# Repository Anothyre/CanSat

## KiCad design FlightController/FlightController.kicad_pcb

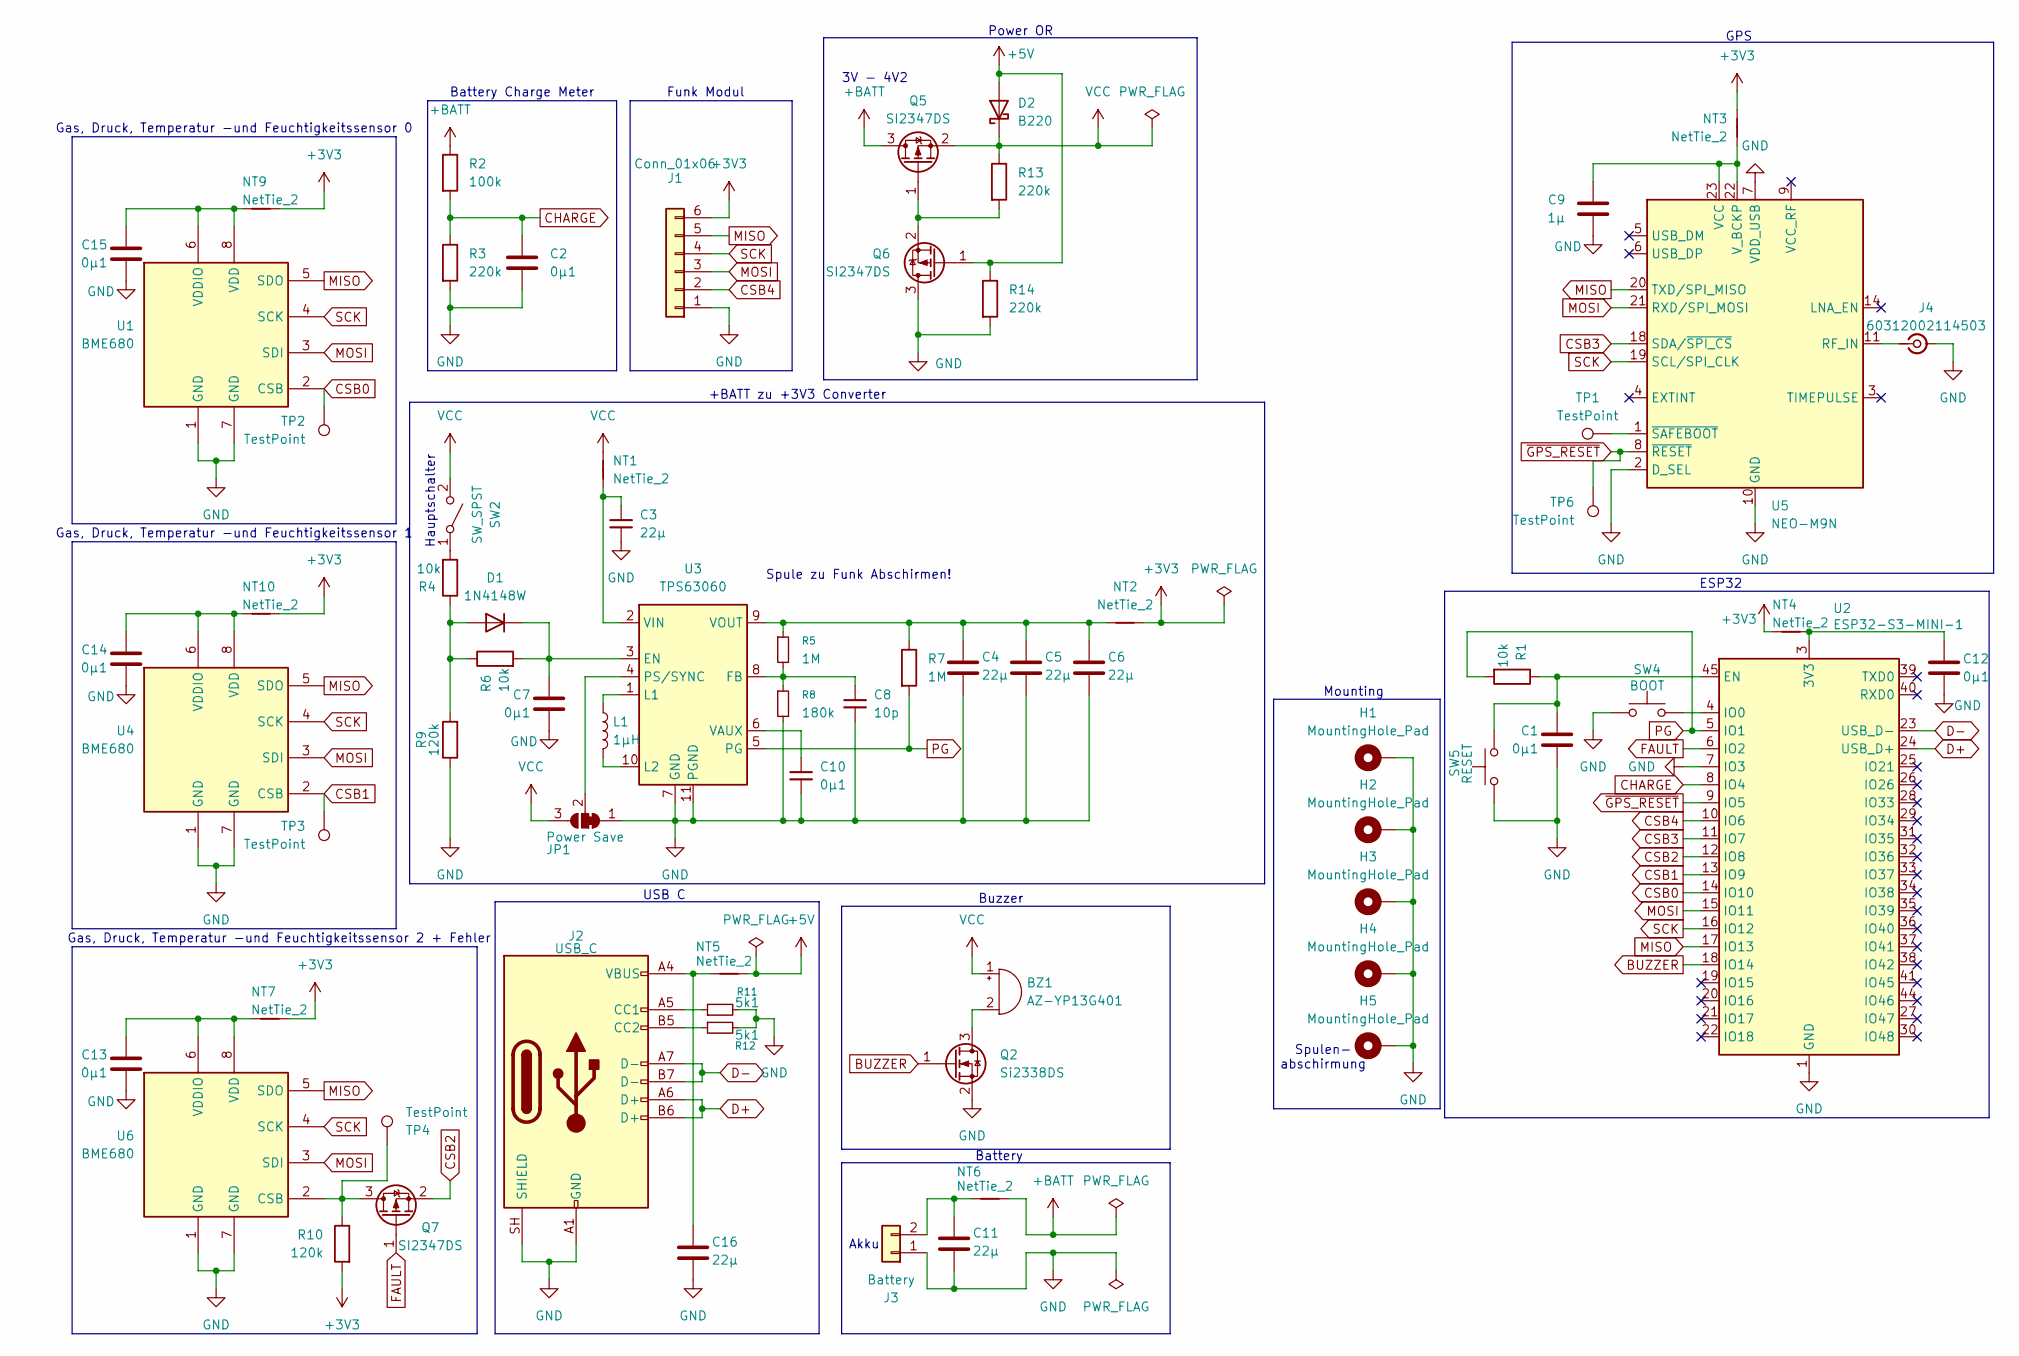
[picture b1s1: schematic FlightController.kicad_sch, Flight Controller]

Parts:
BZ1: AZ-YP13G401; MagneticBuzzer_ProSignal_ABT-410-RC
C1, C2, C7, C10, C12, C13, C14, C15: 0µ1; C_0805_2012Metric_Pad1.18x1.45mm_HandSolder
C3, C4, C5, C6, C11, C16: 22µ; C_0805_2012Metric_Pad1.18x1.45mm_HandSolder
C8: 10p; C_0805_2012Metric_Pad1.18x1.45mm_HandSolder
C9: 1µ; C_0805_2012Metric_Pad1.18x1.45mm_HandSolder
D1: 1N4148W; D_SOD-123
D2: B220; D_SMB
H1, H2, H3, H4: MountingHole_Pad; MountingHole_3.2mm_M3_DIN965_Pad_TopBottom
H5: MountingHole_Pad; MountingHole_2.2mm_M2_DIN965_Pad_TopBottom
J1: Conn_01x06; PinHeader_1x06_P2.54mm_Vertical
J2: USB_C; USB_C_Receptacle_HRO_TYPE-C-31-M-12
J3: Battery; JST-PH-2
J4: 60312002114503; SMA_Wurth_60312002114503_Vertical
JP1: Power Save; SolderJumper-3_P1.3mm_Bridged12_RoundedPad1.0x1.5mm
L1: 1µH; L_Coilcraft_XxL4020
NT1, NT2, NT3, NT4, NT5, NT6, NT7, NT9, NT10: NetTie_2; NetTie-2_SMD_Pad0.5mm
Q2: Si2338DS; SOT-23
Q5, Q6, Q7: SI2347DS; SOT-23
R1, R4, R6: 10k; R_0805_2012Metric_Pad1.20x1.40mm_HandSolder
R2: 100k; R_0805_2012Metric_Pad1.20x1.40mm_HandSolder
R3, R13, R14: 220k; R_0805_2012Metric_Pad1.20x1.40mm_HandSolder
R5, R7: 1M; R_0805_2012Metric_Pad1.20x1.40mm_HandSolder
R8: 180k; R_0805_2012Metric_Pad1.20x1.40mm_HandSolder
R9, R10: 120k; R_0805_2012Metric_Pad1.20x1.40mm_HandSolder
R11, R12: 5k1; R_0805_2012Metric_Pad1.20x1.40mm_HandSolder
SW2: SW_SPST; PinHeader_1x02_P2.54mm_Vertical
SW4: BOOT; SW_Push_5.1mm_H1.5mm
SW5: RESET; SW_Push_5.1mm_H1.5mm
TP1, TP2, TP3, TP4, TP6: TestPoint; TestPoint_Pad_D1.0mm
U1, U4, U6: BME680; Bosch_LGA-8_3x3mm_P0.8mm_ClockwisePinNumbering
U2: ESP32-S3-MINI-1
U3: TPS63060; Texas_DSC0010J_ThermalVias
U5: NEO-M9N; ublox_NEO

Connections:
+5V: D2.2 (A), NT5.2, Q6.1 (G), R14.1
+BATT: NT6.2, Q5.3 (D), R2.1
BUZZER: Q2.1 (G), U2.18 (IO14)
CHARGE: C2.1, R2.2, R3.1, U2.8 (IO4)
CSB0: TP2.1 (1_1), U1.2 (CSB), U2.14 (IO10)
CSB1: TP3.1 (1_1), U2.13 (IO9), U4.2 (CSB)
CSB2: Q7.2 (S), U2.12 (IO8)
CSB3: U2.11 (IO7), U5.18 (SDA/~SPI_CS)
CSB4: J1.2, U2.10 (IO6)
D+: J2.A6 (D+), J2.B6 (D+), U2.24 (USB_D+)
D-: J2.A7 (D-), J2.B7 (D-), U2.23 (USB_D-)
FAULT: Q7.1 (G), U2.6 (IO2)
GND: C1.2, C2.2, C3.2, C4.2, C5.2, C6.2, C7.2, C8.2, C9.2, C10.2, C11.2, C12.2, C13.2, C14.2, C15.2, C16.2, H1.1 (1_1), H2.1 (1_1), H3.1 (1_1), H4.1 (1_1), H5.1 (1_1), J1.1, J2.A1 (GND), J2.A12 (GND), J2.B1 (GND), J2.B12 (GND), J2.SH (SHIELD), J3.1, J4.2 (Ext), JP1.1 (A), Q2.2 (S), Q6.3 (D), R3.2, R8.2, R9.1, R11.2, R12.2, R14.2, SW4.1, SW5.1, U1.1 (GND), U1.7 (GND), U2.1 (GND), U2.2 (GND), U2.7 (IO3), U2.42 (GND), U2.43 (GND), U2.46 (GND), U2.47 (GND), U2.48 (GND), U2.49 (GND), U2.50 (GND), U2.51 (GND), U2.52 (GND), U2.53 (GND), U2.54 (GND), U2.55 (GND), U2.56 (GND), U2.57 (GND), U2.58 (GND), U2.59 (GND), U2.60 (GND), U2.61 (GND), U2.62 (GND), U2.63 (GND), U2.64 (GND), U2.65 (GND), U3.7 (GND), U3.11 (PGND), U4.1 (GND), U4.7 (GND), U5.2 (D_SEL), U5.7 (VDD_USB), U5.10 (GND), U5.12 (GND), U5.13 (GND), U5.24 (GND), U6.1 (GND), U6.7 (GND)
MISO: J1.5, U1.5 (SDO), U2.17 (IO13), U4.5 (SDO), U5.20 (TXD/SPI_MISO), U6.5 (SDO)
MOSI: J1.3, U1.3 (SDI), U2.15 (IO11), U4.3 (SDI), U5.21 (RXD/SPI_MOSI), U6.3 (SDI)
unnamed: BZ1.2 (-), Q2.3 (D)
unnamed: C16.1, J2.A4 (VBUS), J2.A9 (VBUS), J2.B4 (VBUS), J2.B9 (VBUS), NT5.1
unnamed: D1.2 (A), R4.1, R6.1, R9.2
unnamed: C7.1, D1.1 (K), R6.2, U3.3 (EN)
unnamed: J2.A5 (CC1), R11.1
unnamed: J2.B5 (CC2), R12.1
unnamed: C11.1, J3.2, NT6.1
unnamed: J4.1 (In), U5.11 (RF_IN)
unnamed: JP1.2 (C), U3.4 (PS/SYNC)
unnamed: Q5.1 (G), Q6.2 (S), R13.2
unnamed: Q7.3 (D), R10.1, TP4.1 (1_1), U6.2 (CSB)
unnamed: R4.2, SW2.1 (A)
unnamed: C15.1, NT9.1, U1.6 (VDDIO), U1.8 (VDD)
unnamed: C12.1, NT4.2, U2.3 (3V3)
unnamed: C1.1, R1.1, SW5.2, U2.45 (EN)
unnamed: SW4.2, U2.4 (IO0)
unnamed: C8.1, R5.2, R8.1, U3.8 (FB)
unnamed: L1.1, U3.1 (L1)
unnamed: L1.2, U3.10 (L2)
unnamed: C10.1, U3.6 (VAUX)
unnamed: C3.1, NT1.1, U3.2 (VIN)
unnamed: C4.1, C5.1, C6.1, NT2.1, R5.1, R7.1, U3.9 (VOUT)
unnamed: C14.1, NT10.1, U4.6 (VDDIO), U4.8 (VDD)
unnamed: C9.1, NT3.1, U5.22 (V_BCKP), U5.23 (VCC)
unnamed: TP1.1 (1_1), U5.1 (~SAFEBOOT)
unnamed: C13.1, NT7.1, U6.6 (VDDIO), U6.8 (VDD)
SCK: J1.4, U1.4 (SCK), U2.16 (IO12), U4.4 (SCK), U5.19 (SCL/SPI_CLK), U6.4 (SCK)
VCC: BZ1.1 (+), D2.1 (K), JP1.3 (B), NT1.2, Q5.2 (S), R13.1, SW2.2 (B)
~GPS_RESET: TP6.1 (1_1), U2.9 (IO5), U5.8 (~RESET)

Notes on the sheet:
Battery Charge Meter
Power OR
USB C
Spule zu Funk Abschirmen!
+BATT zu +3V3 Converter
ESP32
3V - 4V2
Funk Modul
Gas, Druck, Temperatur -und Feuchtigkeitssensor 1
Gas, Druck, Temperatur -und Feuchtigkeitssensor 2 + Fehler
Gas, Druck, Temperatur -und Feuchtigkeitssensor 0
Akku
Mounting
Hauptschalter
GPS
Buzzer
Spulen- abschirmung
Battery

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
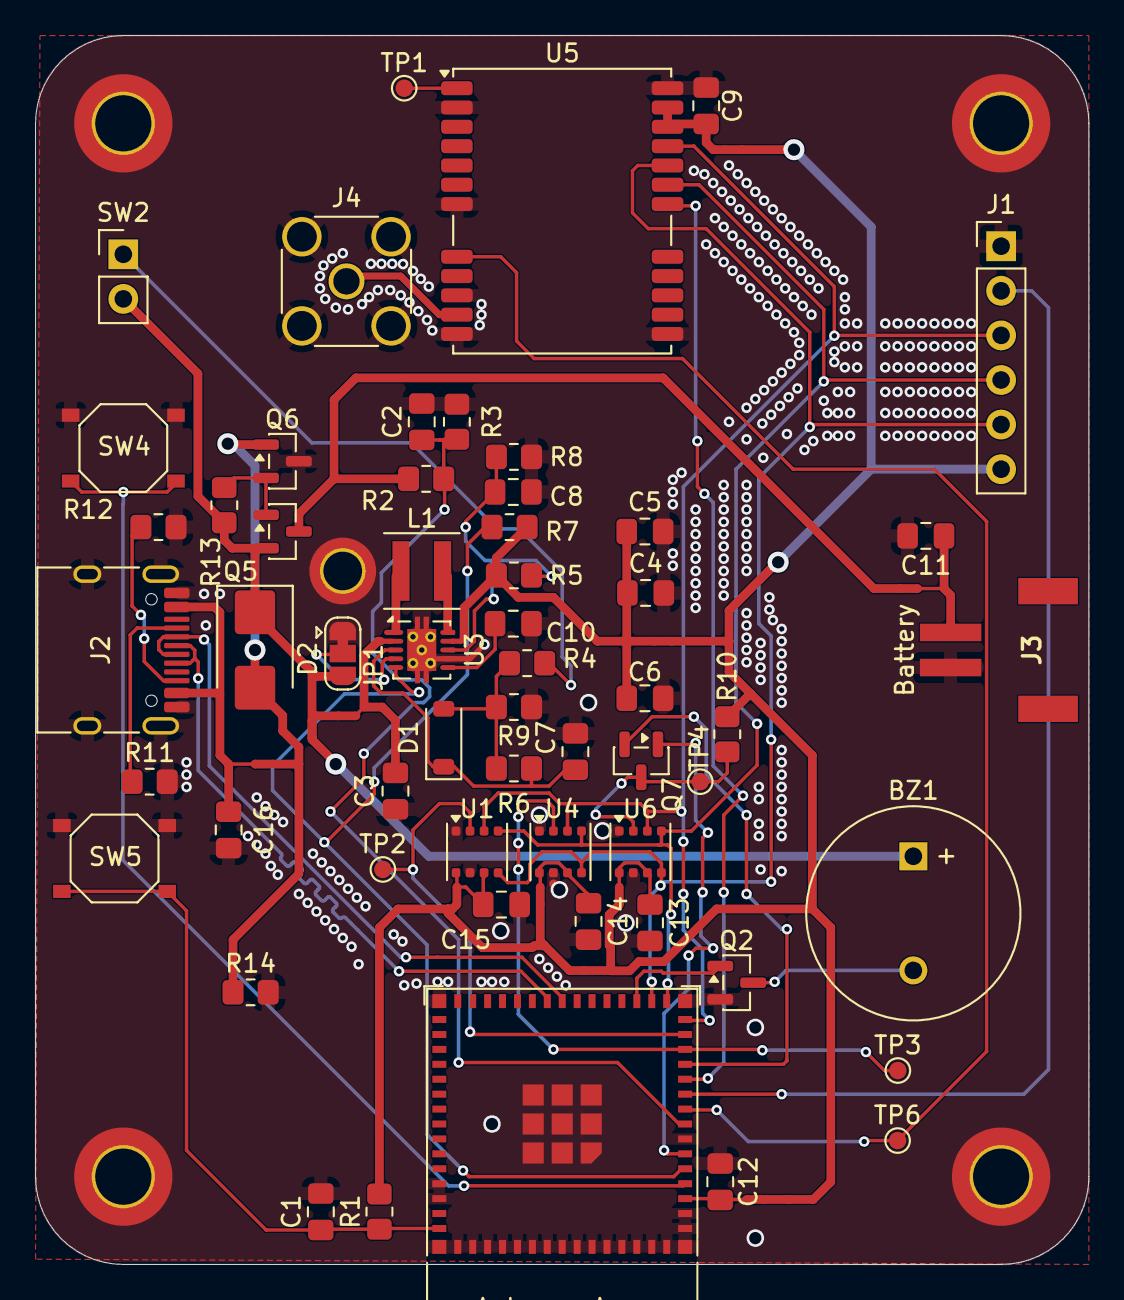
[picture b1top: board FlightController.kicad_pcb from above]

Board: 2 copper layers, 60.0 x 70.0 mm, 71 parts (0 on the bottom side), 46 nets.

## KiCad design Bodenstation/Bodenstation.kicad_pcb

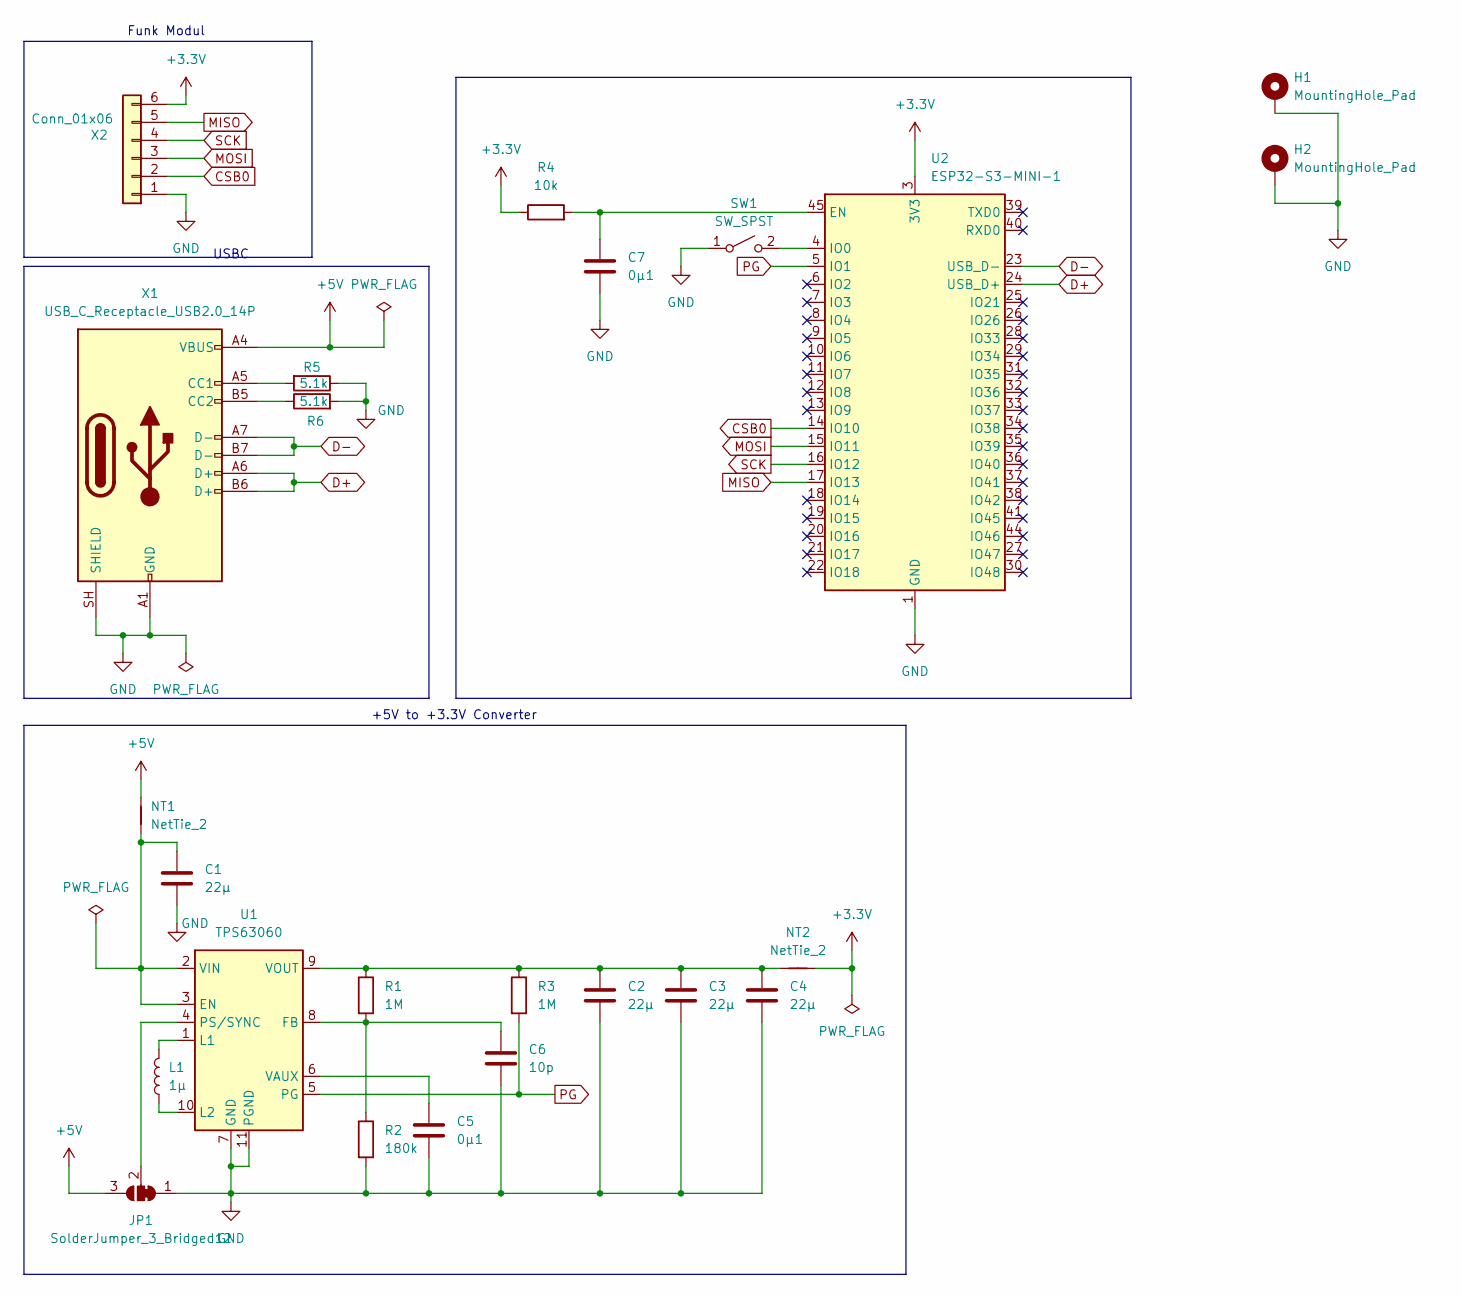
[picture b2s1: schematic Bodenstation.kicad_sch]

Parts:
C1, C2, C3, C4: 22µ; C_0805_2012Metric_Pad1.18x1.45mm_HandSolder
C5, C7: 0µ1; C_0805_2012Metric_Pad1.18x1.45mm_HandSolder
C6: 10p; C_0805_2012Metric_Pad1.18x1.45mm_HandSolder
H1, H2: MountingHole_Pad; MountingHole_3.2mm_M3
JP1: SolderJumper_3_Bridged12; WSON-8-1EP_6x5mm_P1.27mm_EP3.4x4mm
L1: 1µ; L_Coilcraft_XxL4020
NT1, NT2: NetTie_2; NetTie-2_SMD_Pad0.5mm
R1, R3: 1M; R_0805_2012Metric_Pad1.20x1.40mm_HandSolder
R2: 180k; R_0805_2012Metric_Pad1.20x1.40mm_HandSolder
R4: 10k; R_0805_2012Metric_Pad1.20x1.40mm_HandSolder
R5, R6: 5.1k; R_0805_2012Metric_Pad1.20x1.40mm_HandSolder
SW1: SW_SPST; SW_Push_5.1mm_H1.5mm
U1: TPS63060; Texas_S-PWSON-N10_ThermalVias
U2: ESP32-S3-MINI-1; ESP32-S2-MINI-1
X1: USB_C_Receptacle_USB2.0_14P; USB_C_Receptacle_HRO_TYPE-C-31-M-12
X2: Conn_01x06; PinHeader_1x06_P2.54mm_Vertical

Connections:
+3.3V: NT2.1, R4.1, U2.3 (3V3), X2.6
+5V: JP1.3 (B), NT1.2, X1.A4 (VBUS), X1.A9 (VBUS), X1.B4 (VBUS), X1.B9 (VBUS)
CSB0: U2.14 (IO10), X2.2
D+: U2.24 (USB_D+), X1.A6 (D+), X1.B6 (D+)
D-: U2.23 (USB_D-), X1.A7 (D-), X1.B7 (D-)
GND: C1.2, C2.2, C3.2, C4.2, C5.2, C6.2, C7.2, H1.1, H2.1, JP1.1 (A), R2.2, R5.1, R6.2, SW1.1 (A), U1.7 (GND), U1.11 (PGND), U2.1 (GND), U2.2 (GND), U2.42 (GND), U2.43 (GND), U2.46 (GND), U2.47 (GND), U2.48 (GND), U2.49 (GND), U2.50 (GND), U2.51 (GND), U2.52 (GND), U2.53 (GND), U2.54 (GND), U2.55 (GND), U2.56 (GND), U2.57 (GND), U2.58 (GND), U2.59 (GND), U2.60 (GND), U2.61 (GND), U2.62 (GND), U2.63 (GND), U2.64 (GND), U2.65 (GND), X1.A1 (GND), X1.A12 (GND), X1.B1 (GND), X1.B12 (GND), X1.SH (SHIELD), X2.1
MISO: U2.17 (IO13), X2.5
MOSI: U2.15 (IO11), X2.3
unnamed: JP1.2 (C), U1.4 (PS/SYNC)
unnamed: SW1.2 (B), U2.4 (IO0)
unnamed: C1.1, NT1.1, U1.2 (VIN), U1.3 (EN)
unnamed: C6.1, R1.2, R2.1, U1.8 (FB)
unnamed: L1.2, U1.1 (L1)
unnamed: L1.1, U1.10 (L2)
unnamed: C5.1, U1.6 (VAUX)
unnamed: C2.1, C3.1, C4.1, NT2.2, R1.1, R3.1, U1.9 (VOUT)
unnamed: C7.1, R4.2, U2.45 (EN)
unnamed: R5.2, X1.A5 (CC1)
unnamed: R6.1, X1.B5 (CC2)
PG: R3.2, U1.5 (PG), U2.5 (IO1)
SCK: U2.16 (IO12), X2.4

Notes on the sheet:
+5V to +3.3V Converter
USBC
Funk Modul

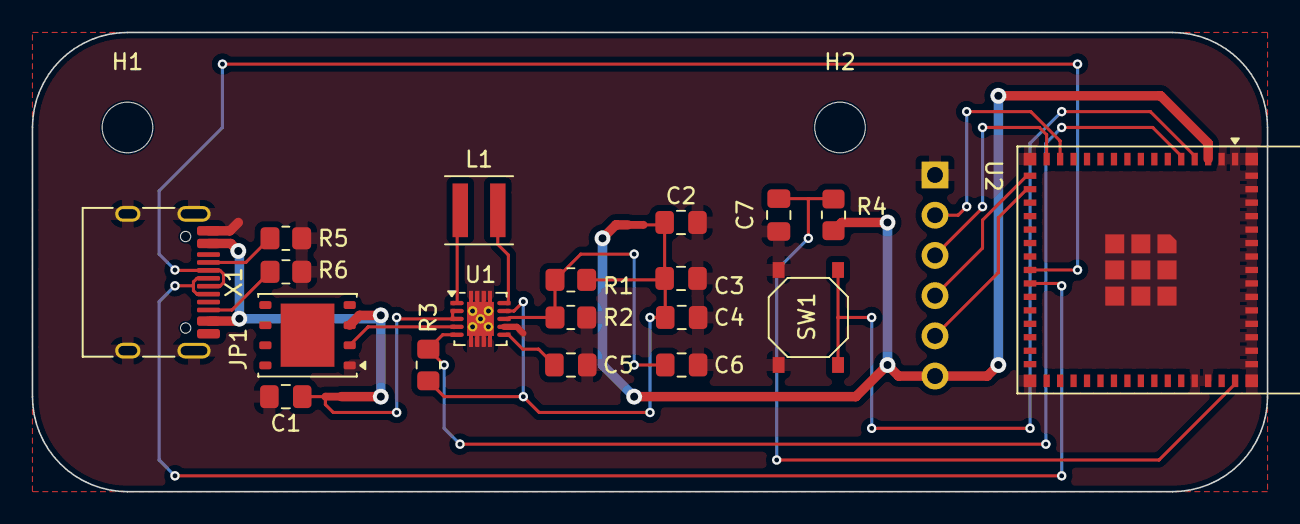
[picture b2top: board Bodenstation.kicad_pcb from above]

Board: 2 copper layers, 78.0 x 29.0 mm, 24 parts (1 on the bottom side), 21 nets.

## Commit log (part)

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2026-06-23 Init KiCAD Project with PI 0 Template
2026-06-23 Configure KiCAD Project
